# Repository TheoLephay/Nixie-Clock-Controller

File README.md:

# Nixie clock - Divergence Meter

I wanted to make a 8-tube design to match Steins Gate's divergence meter and to have more display capabilities.

This is build with original IN-14 (180VDC) Nixie tubes manufactured in the 70s in the Soviet Union.

## How to use

- On power on, if a wifi access point has been provided before, it will try to connect to it.
- Otherwise (if no AP, or if connection fails) it will display blinking dots and it will turn into an access point named "ESP32_Nixie".
  Connect to it, open the clock's IP on a web page, and provide wifi SSID and password. The clock will then
  try to connect to the provided wifi AP.
- It will start displaying the time. You can press the toggle swith (long or short press) to change modes.

## How to build

There should be most of the design files for software and hardware to reproduce it.

Except:
- Tubes that I bought on Ebay
- The BOM is not exaclty complete but all the electronics to build the PCB are there. What's missing is
    - the Molex ribbon cables (check the reference of the connectors and find the matching ones)
    - few pin headers and jumpers
- The case that is home made with some very specific tools.

---

## Hardware

See hardware/*.pdf for the design sheet and layer views. All Kicad design files should be present to build them and the gerber files.

key facts:

- Made for 8 IN-14 tubes
- HV DCDC generator made on board, based on [this design](https://nick.desmith.net/Electronics/NixiePSU.html)
- HV open drain shift registers HV5622 (no multiplexing)
- ESP32C3 module
- Most of the components are solderable with a soldering iron (except the ESP32 because of the pads underneath, heat gun or hot plate required + stencil)

#### Version 1.1 updates:

Fixed HV5622 footprint, used a bigger DCDC FET (Vds rated >250V), Reduced GPIO9 cap size to avoid starting in DL mode, and added PD resistors to the level shifters' NFETs.

### Issues

The feedback line of the DCDC is picking up noise which creates a visible dimming oscillation at around 20Hz (50Vpp). At high load it even makes the DCDC saturate.
I fixed it by adding a small cap (100pF) on FB pin. 0603 size is perfect to sit between SHDN and FB pins of the MAX1771.

My DCDC has only a ~70% efficiency which is not super good compared to the original design (85%), I probably did a poor layout job. But in practice it does not matter since currents involved are small.

## Software

key facts:

- Using ESP-IDF VSCode extension v5.2.1
- Programming via UART (two buttons on the board to get the ESP in download mode)
- Has a "maintenance" routine timer to cycle the cathodes lit to prevent cathode poisonning.

More modes to be coming (with a connected weather station it will be able to display temp/HR...).

- main/src/Connectivity.c - wifi state machine, mDNS & SNTP setup.
- main/src/HV5622.c - Bit banging shift register driver.
- main/src/ModeSwitch.c - Driver for the toggle switch.
- main/src/NixieDisplay.c - simple driver to display data on the 8 tubes using the shift registers.
- main/src/NixieHttpServer.c - Web control page
- main/src/SmartClock.c - core logic of the clock to display time, handle different modes.
- main/src/Storage.c - NVS wrapper for storing wifi credentials.

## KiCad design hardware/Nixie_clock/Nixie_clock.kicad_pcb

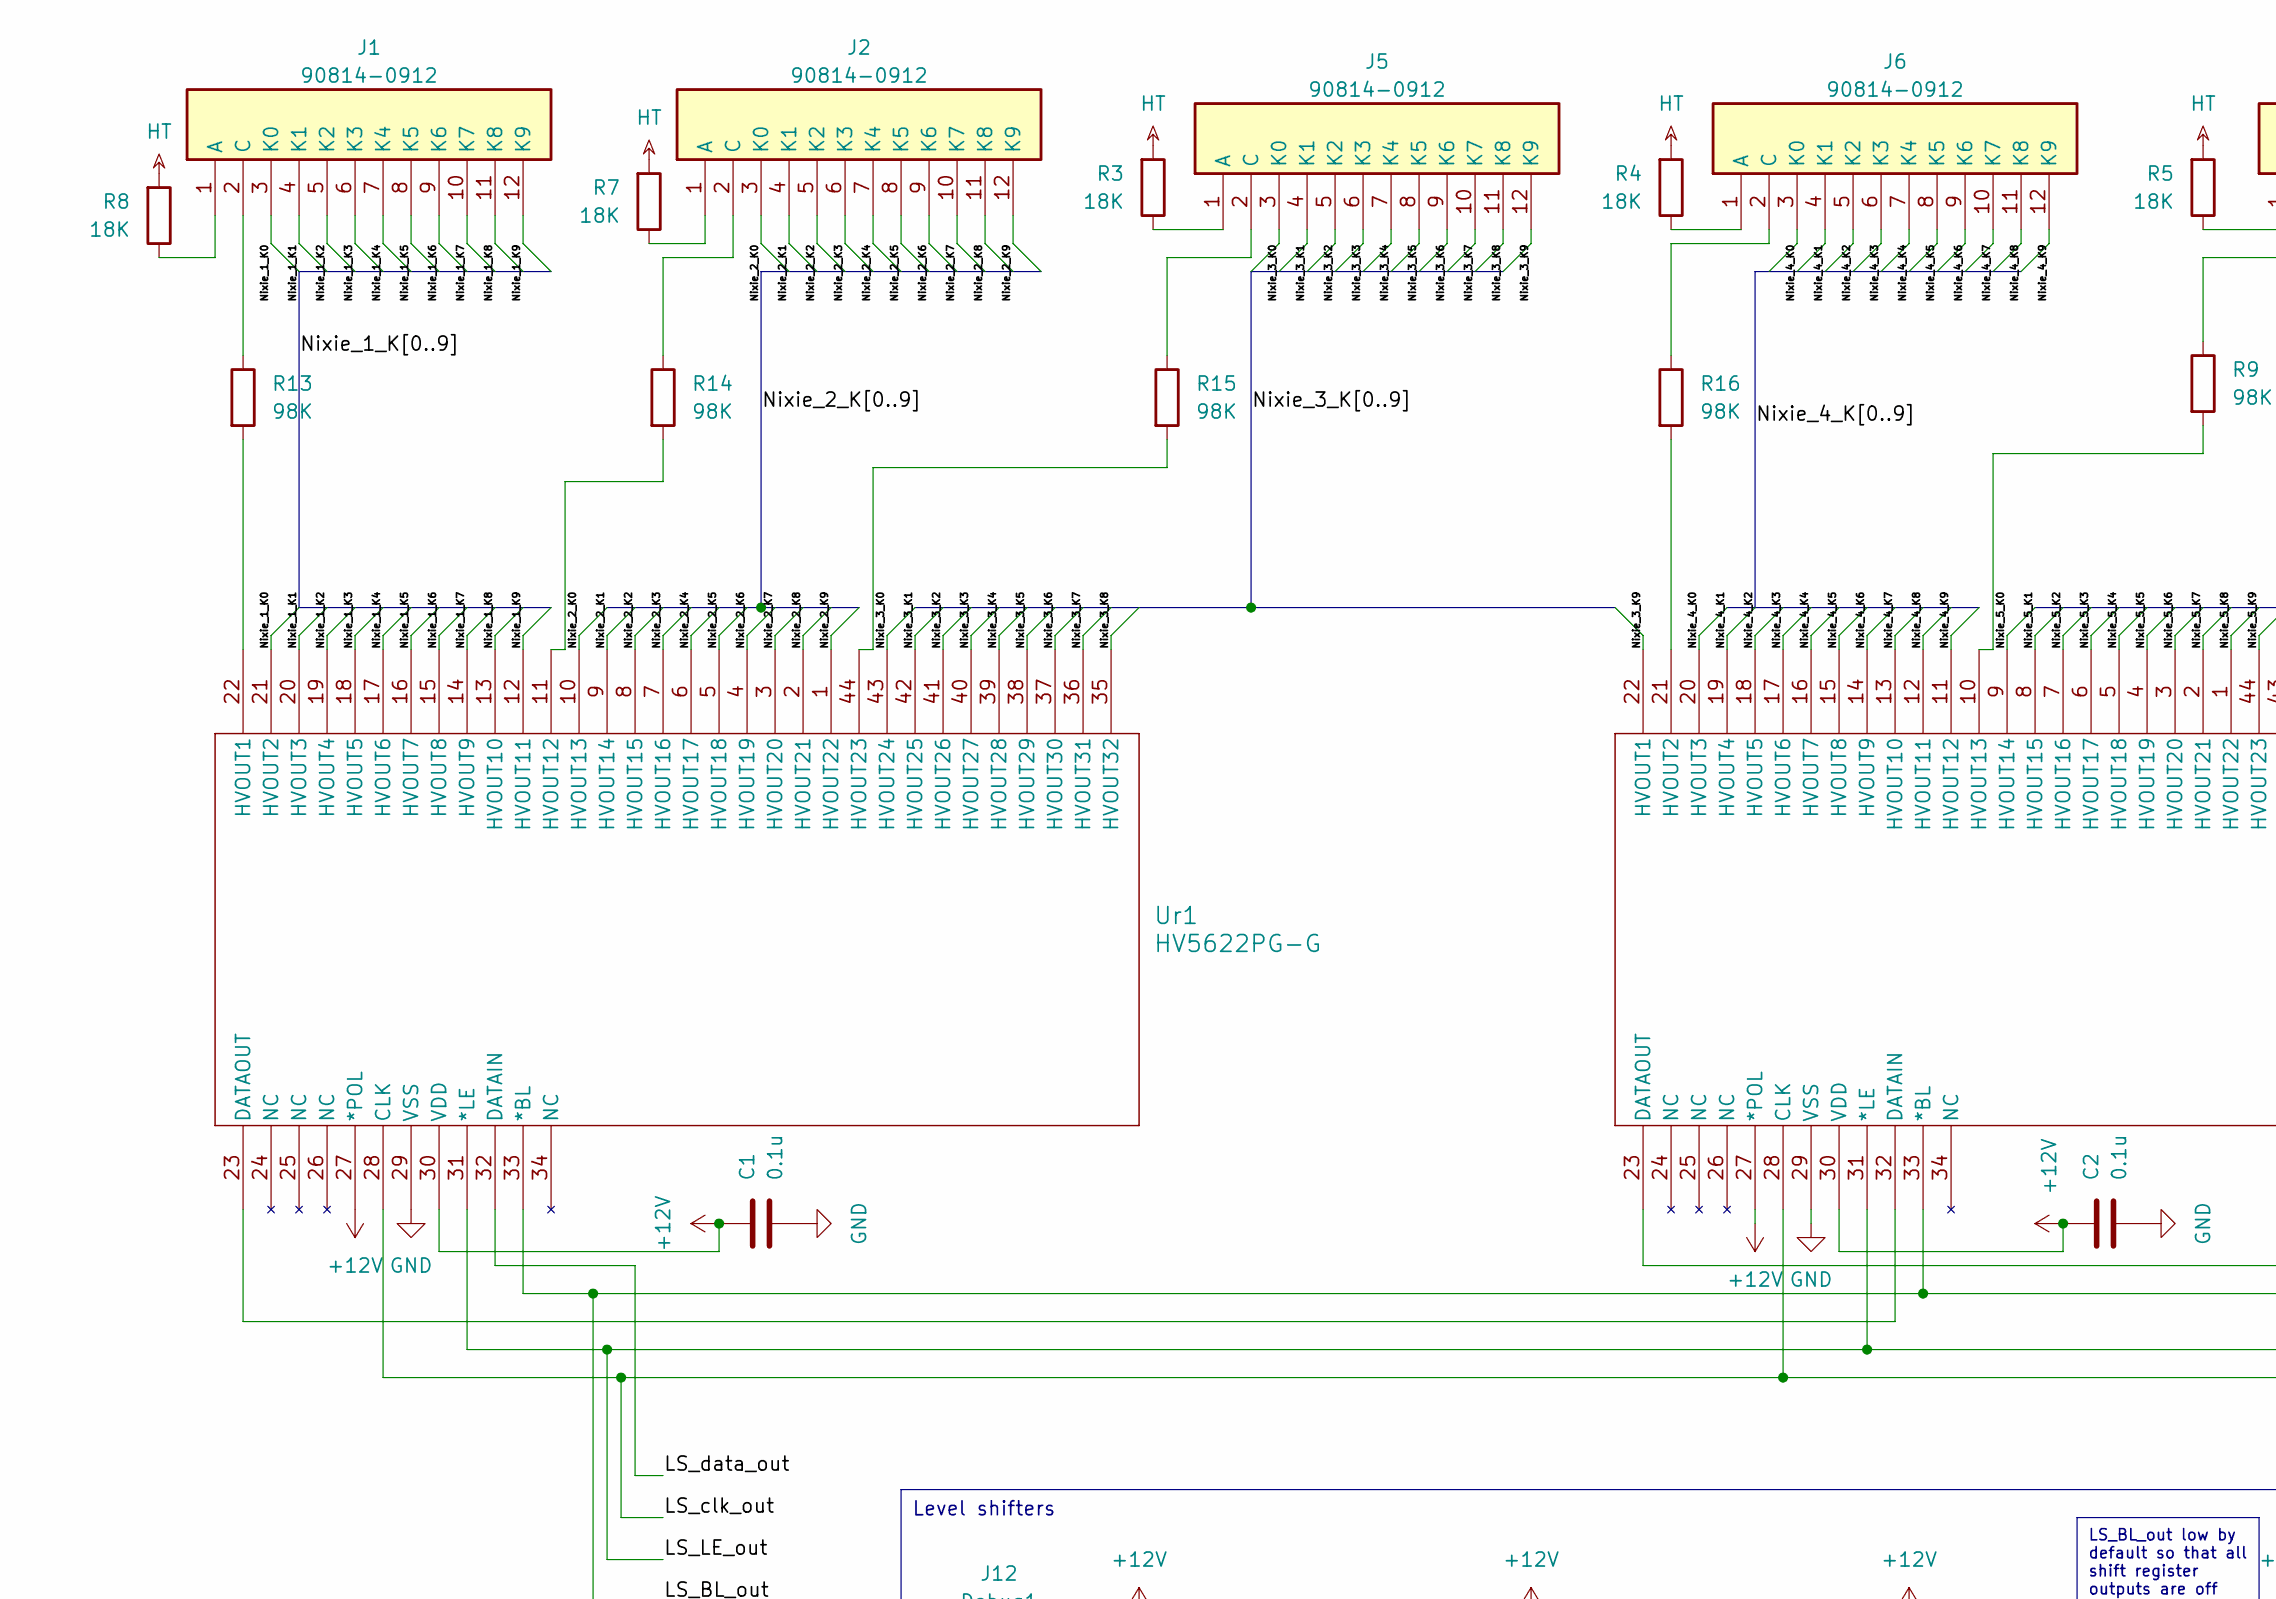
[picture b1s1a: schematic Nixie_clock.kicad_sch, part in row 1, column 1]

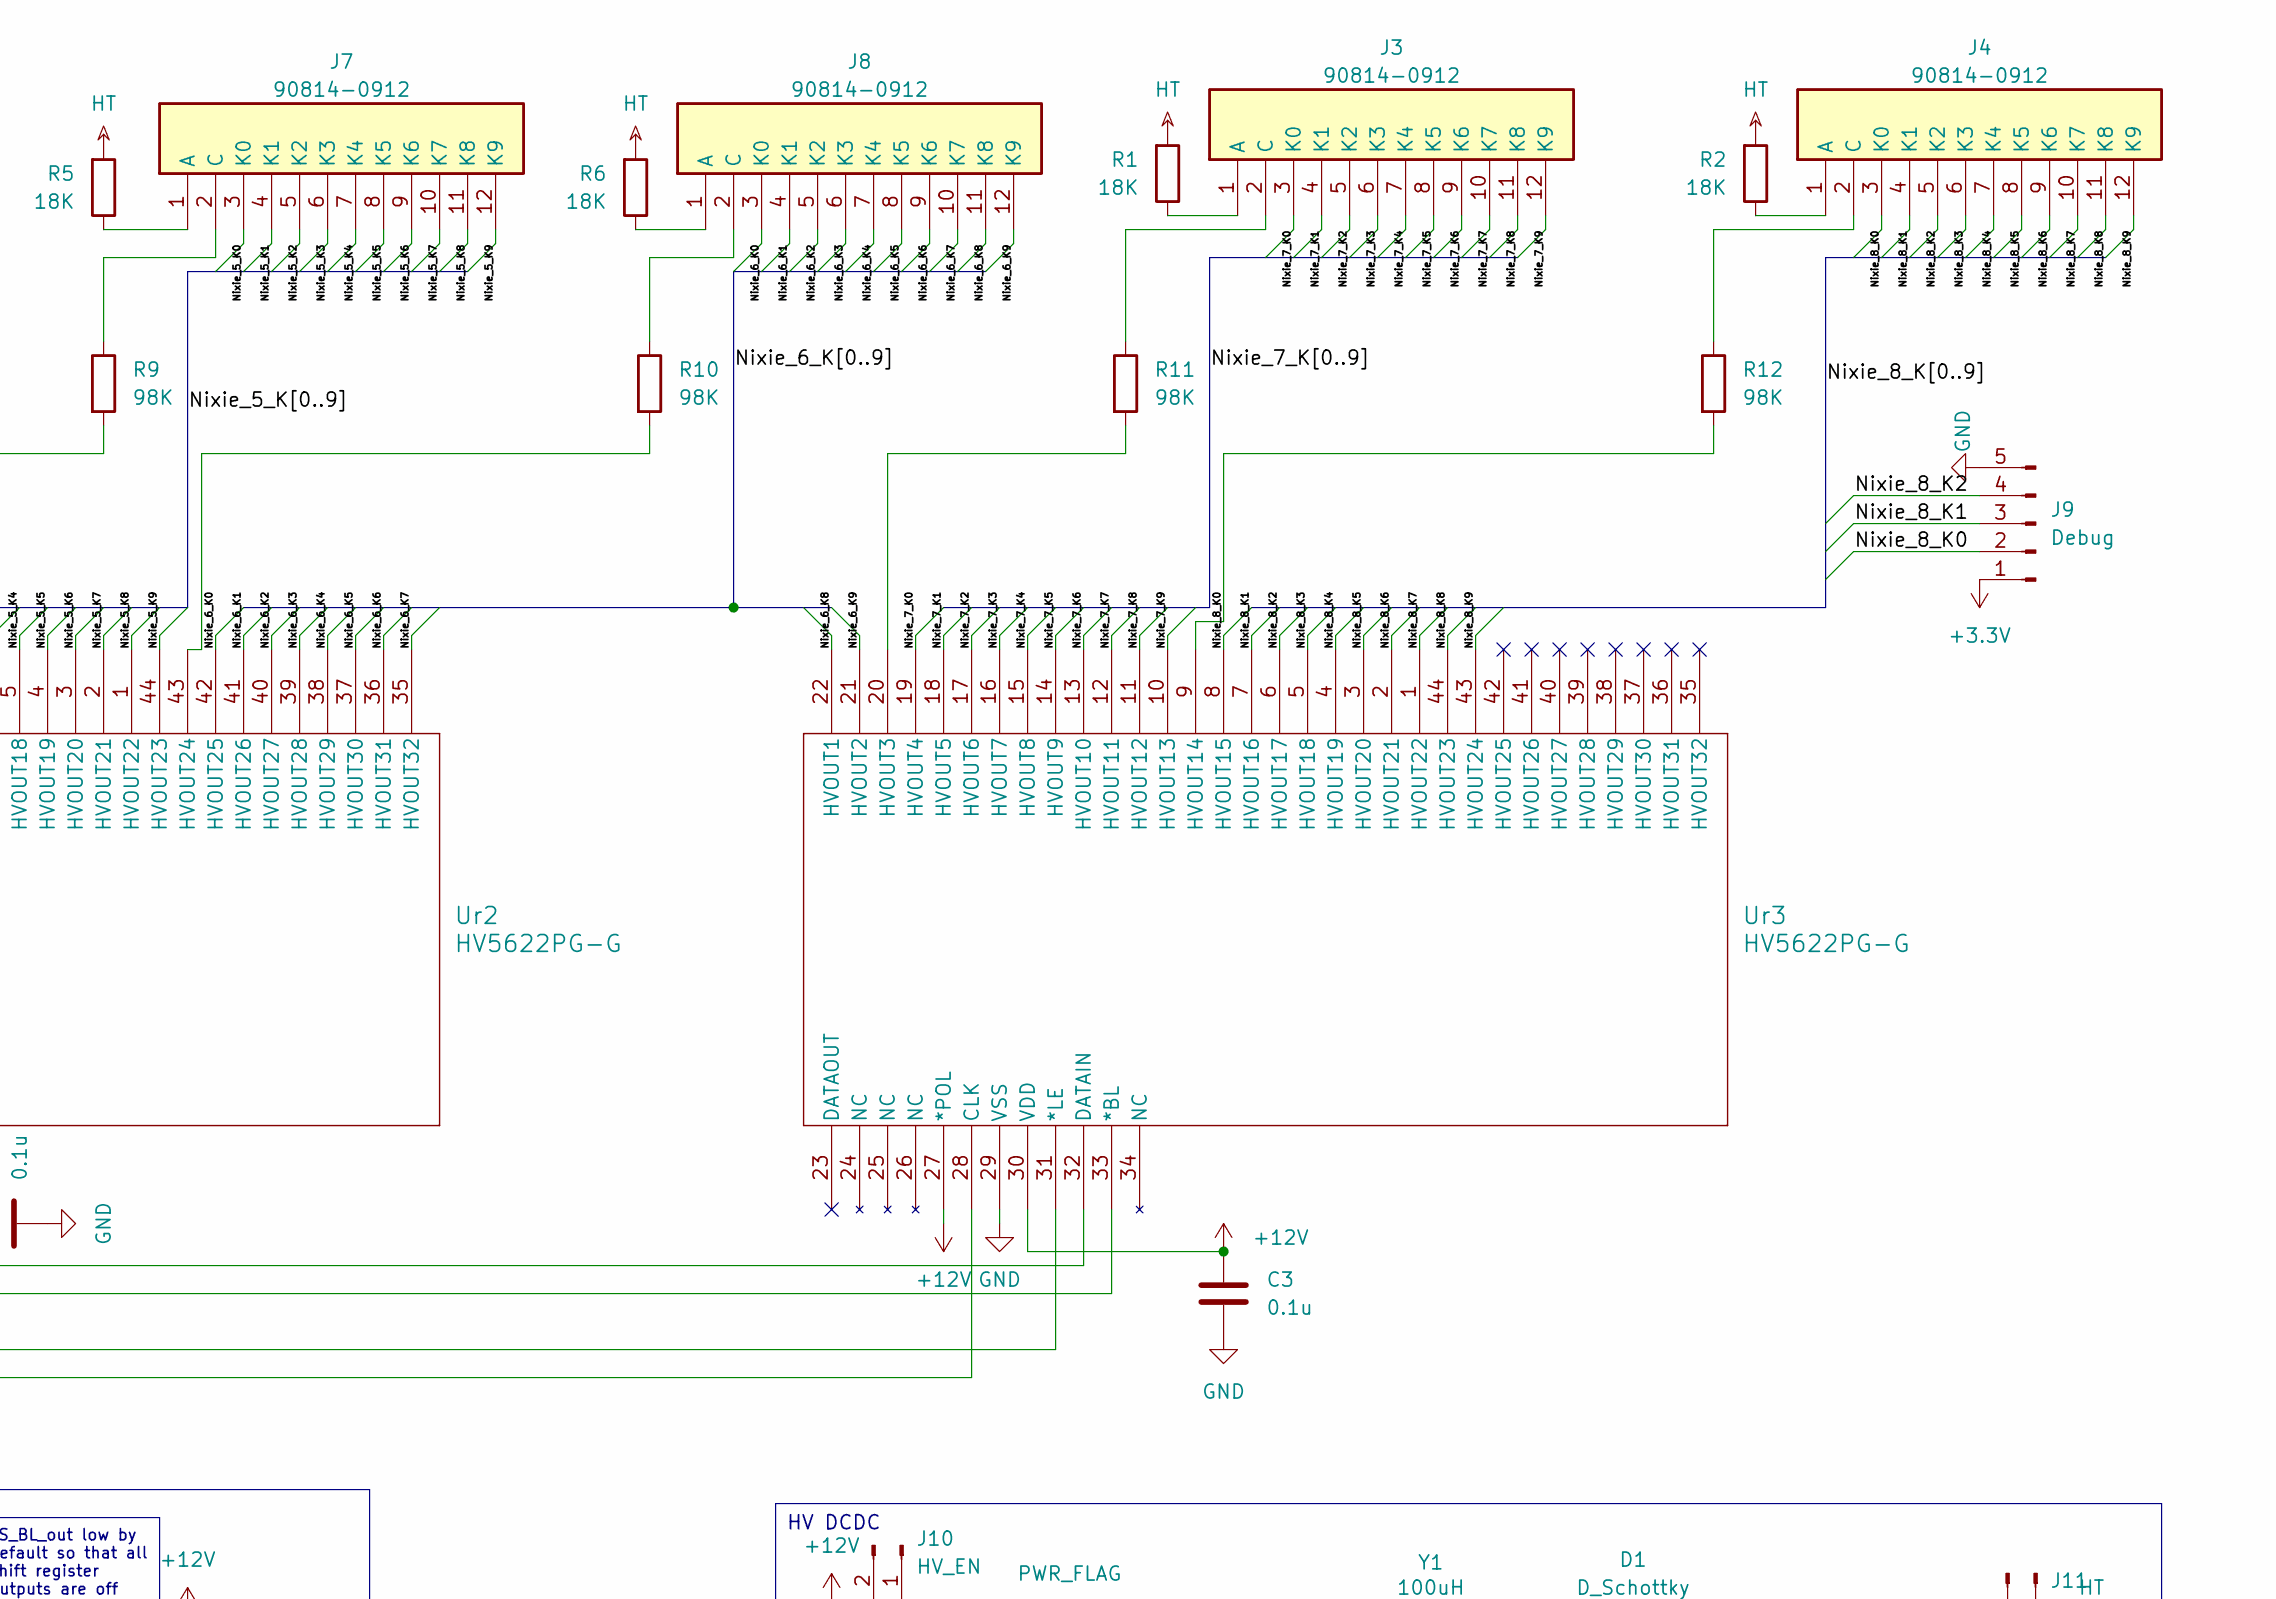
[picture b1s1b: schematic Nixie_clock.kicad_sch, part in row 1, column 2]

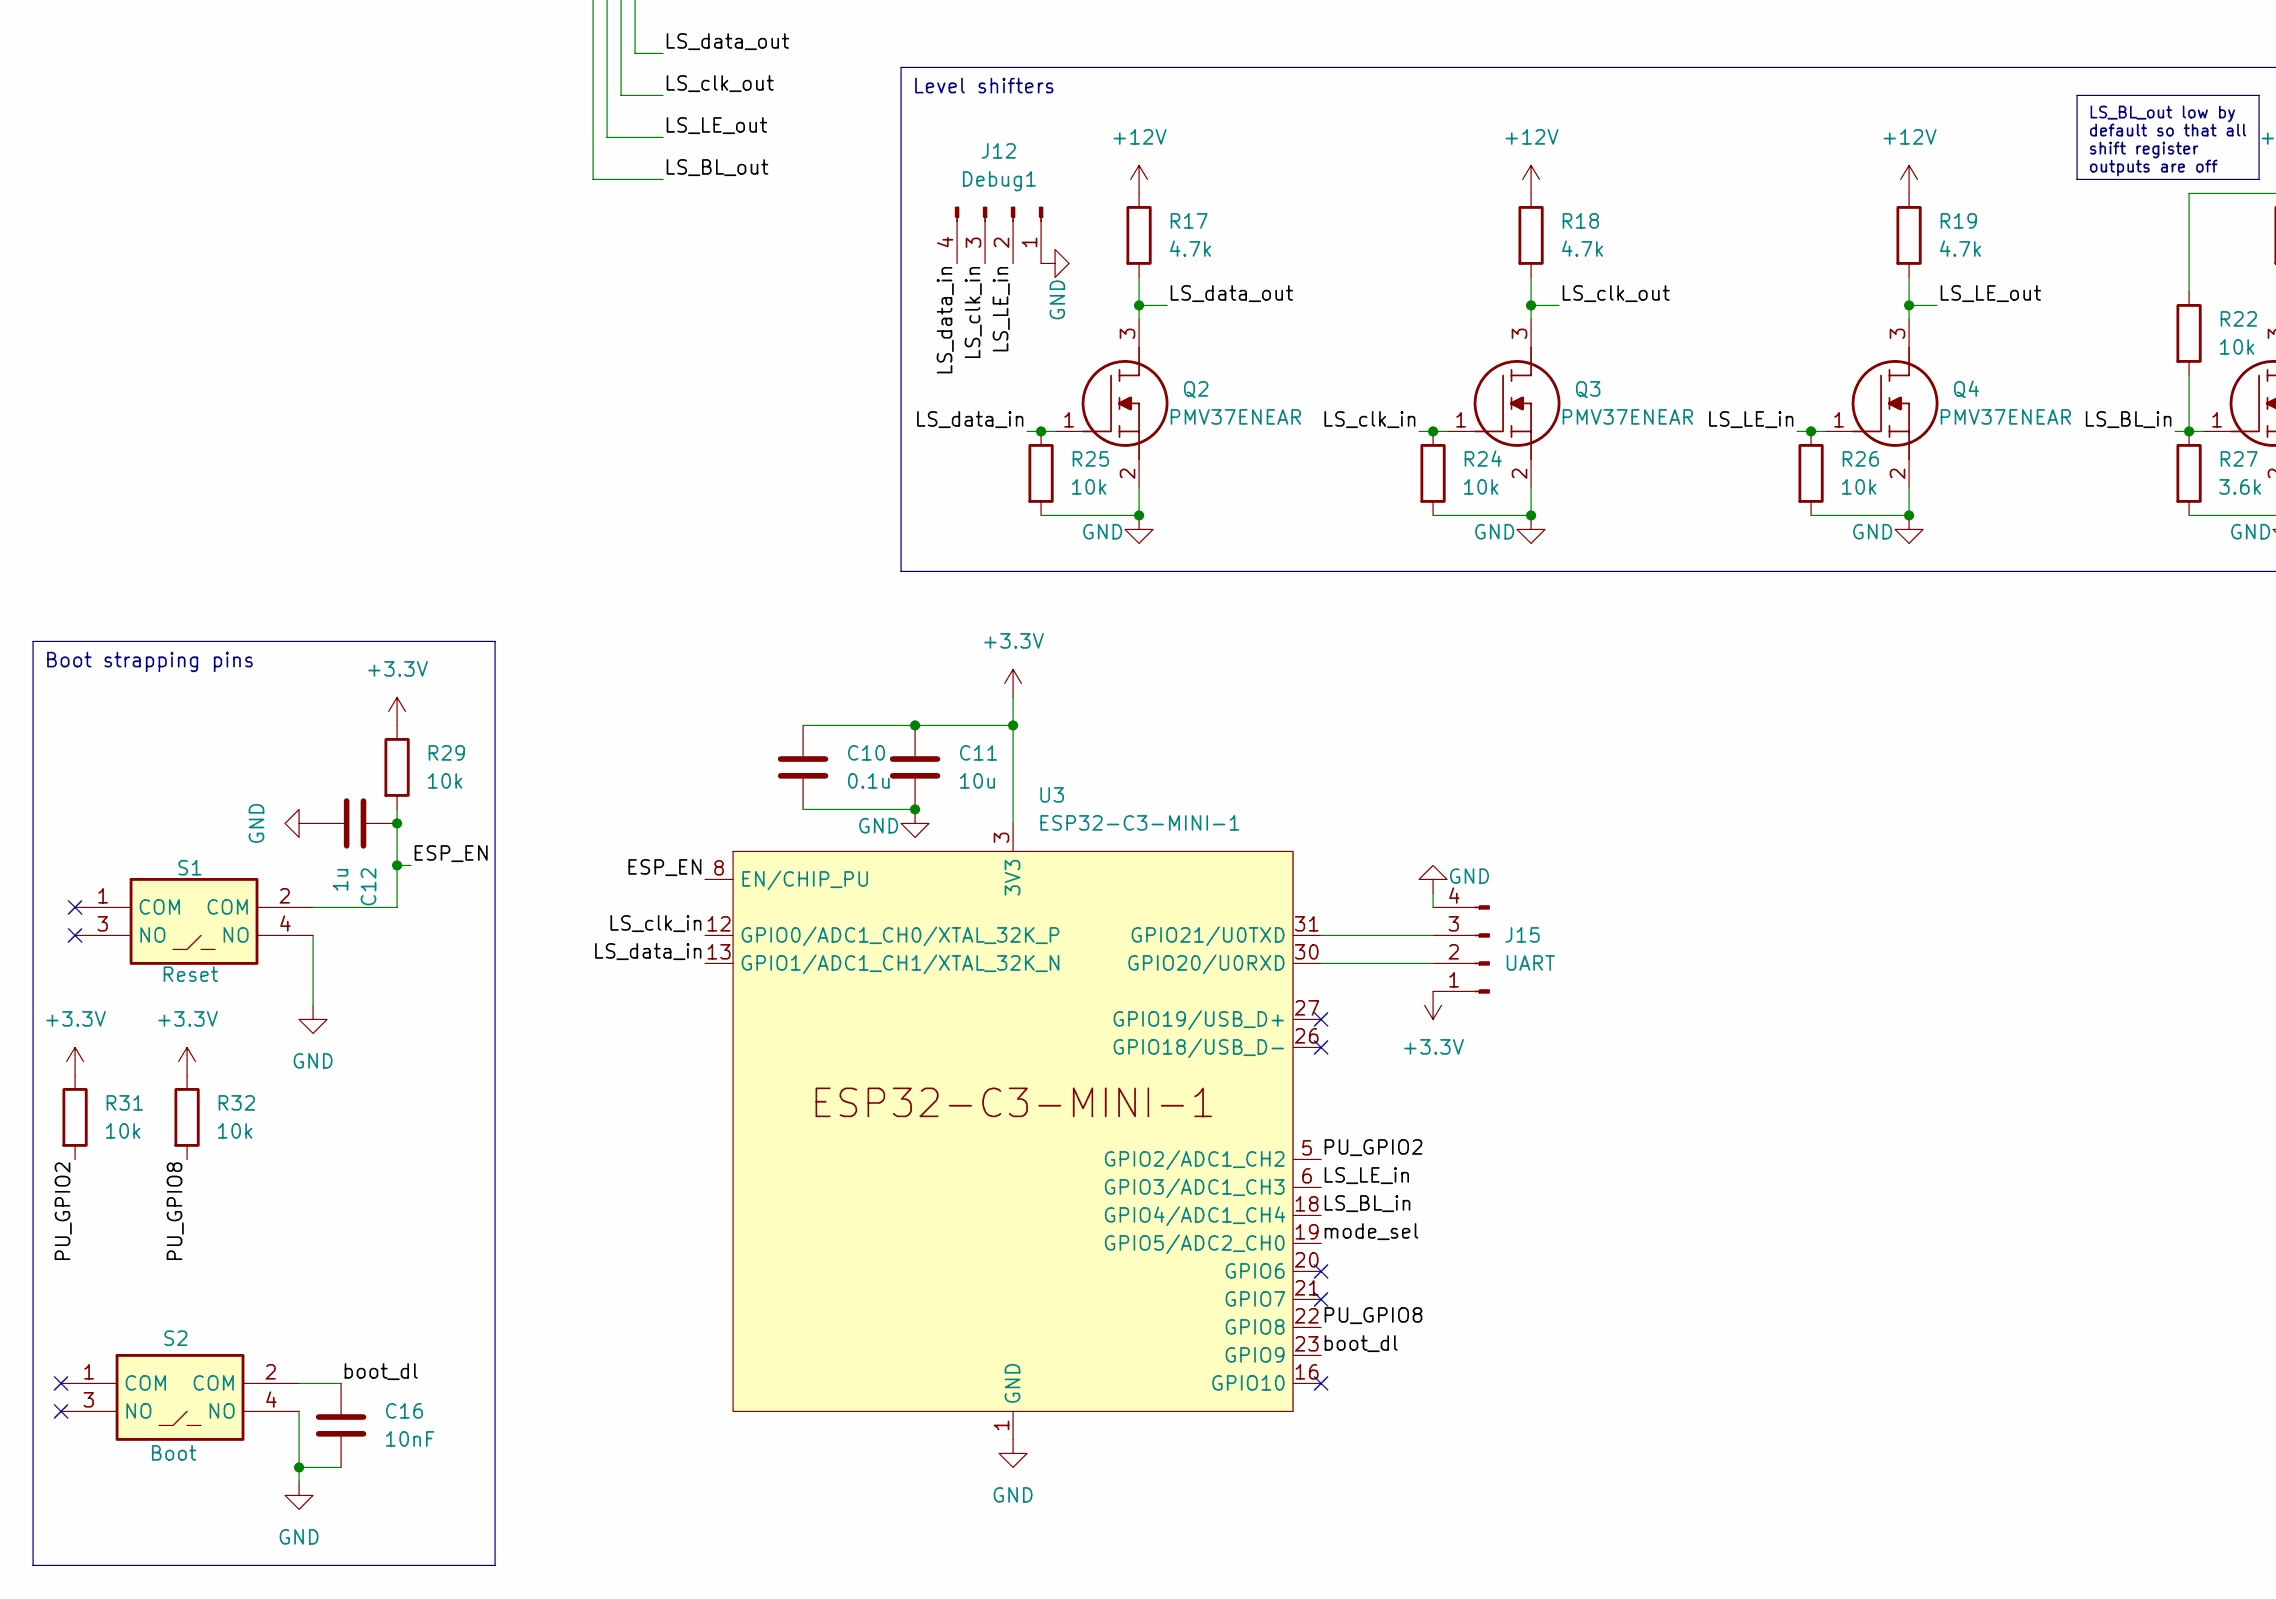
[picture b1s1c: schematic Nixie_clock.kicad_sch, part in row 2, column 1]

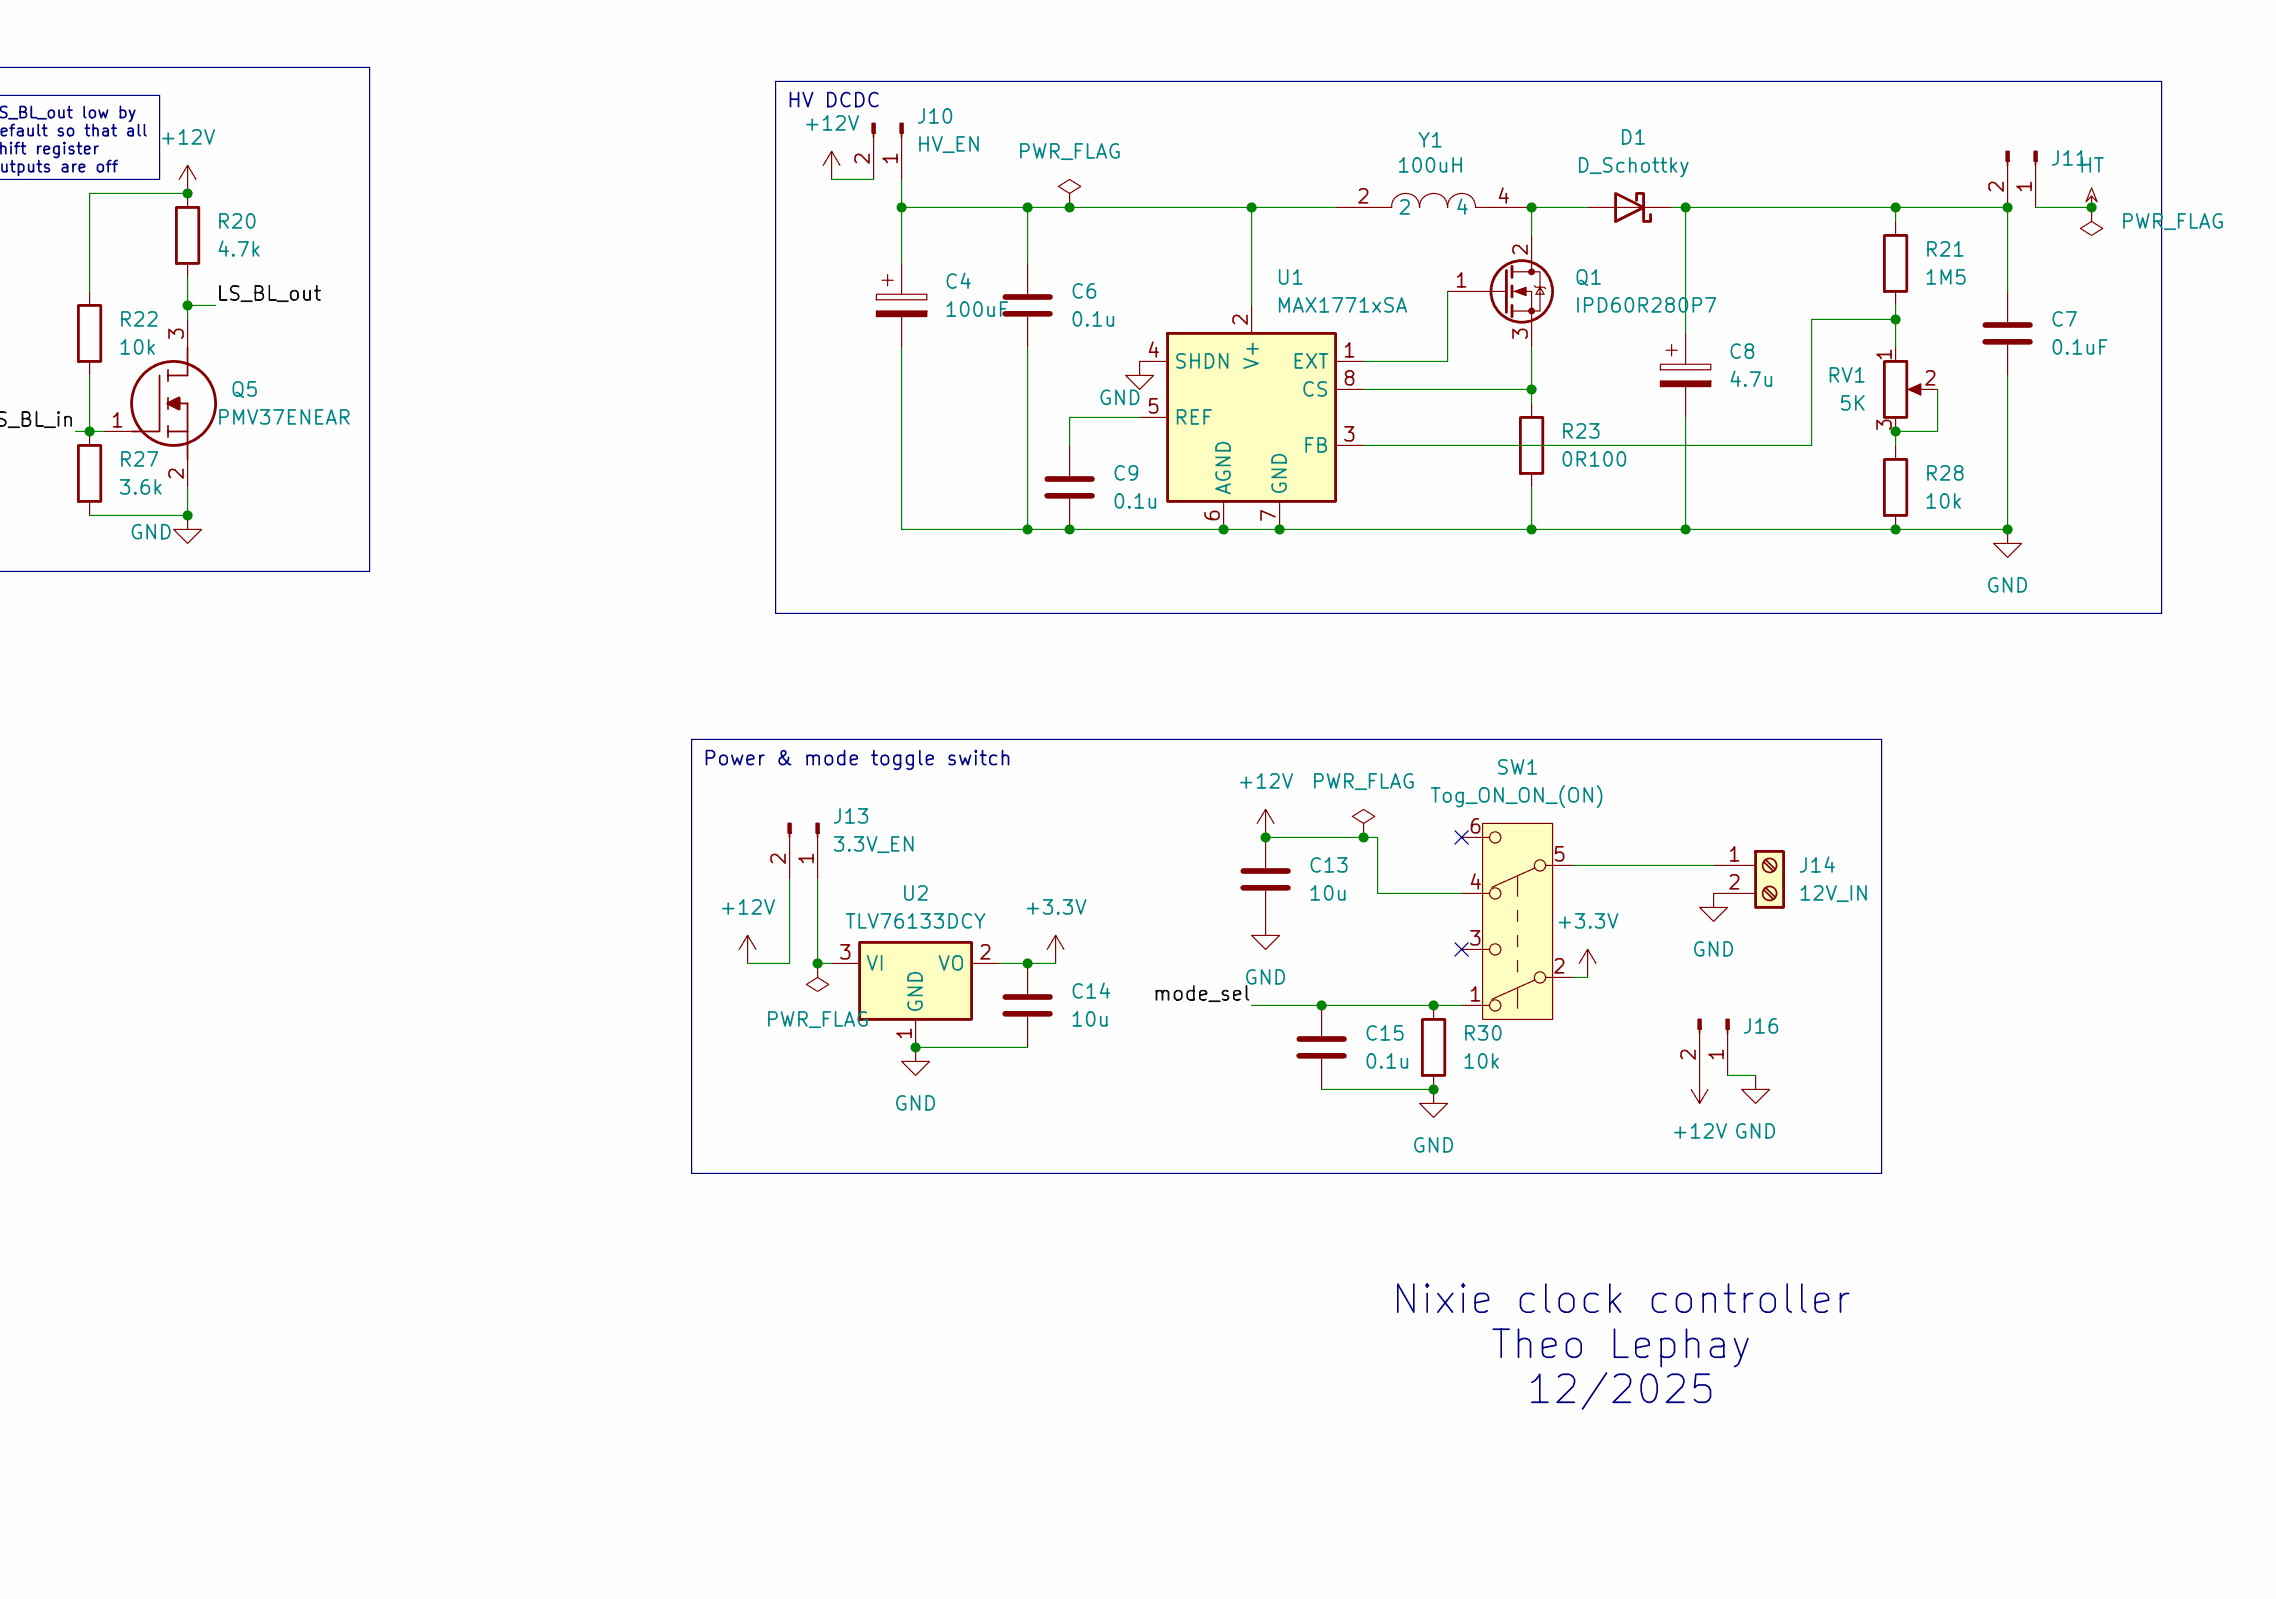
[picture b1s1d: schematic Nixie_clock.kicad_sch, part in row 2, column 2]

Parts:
C1, C2, C3, C6, C9, C10, C15: 0.1u; C_1206_3216Metric_Pad1.33x1.80mm_HandSolder
C4: 100uF; CP_EIA-7343-31_Kemet-D_HandSolder
C7: 0.1uF; C_1206_3216Metric_Pad1.33x1.80mm_HandSolder
C8: 4.7u; CP_Radial_D8.0mm_P3.50mm
C11, C13, C14: 10u; C_1206_3216Metric_Pad1.33x1.80mm_HandSolder
C12: 1u; C_1206_3216Metric_Pad1.33x1.80mm_HandSolder
C16: 10nF; C_1206_3216Metric_Pad1.33x1.80mm_HandSolder
D1: D_Schottky; D_2010_5025Metric_Pad1.52x2.65mm_HandSolder
J1, J2, J3, J4, J5, J6, J7, J8: 90814-0912; Molex_Picoflex_90814-0012_2x06_P1.27mm_Vertical; Mouser Part Number 538-90814-0912
J9: Debug; PinHeader_1x05_P2.54mm_Vertical
J10: HV_EN; PinHeader_1x02_P2.54mm_Vertical
J11, J16: Conn_01x02_Pin; PinHeader_1x02_P2.54mm_Vertical
J12: Debug1; PinHeader_1x04_P2.54mm_Vertical
J13: 3.3V_EN; PinHeader_1x02_P2.54mm_Vertical
J14: 12V_IN; TerminalBlock_MaiXu_MX126-5.0-02P_1x02_P5.00mm
J15: UART; PinSocket_1x04_P2.54mm_Horizontal
Q1: IPD60R280P7; TO-252-2
Q2, Q3, Q4, Q5: PMV37ENEAR; SOT95P230X110-3N; Mouser Part Number 771-PMV37ENEAR
R1, R2, R3, R4, R5, R6, R7, R8: 18K; R_1206_3216Metric_Pad1.30x1.75mm_HandSolder
R9, R10, R11, R12, R13, R14, R15, R16: 98K; R_1206_3216Metric_Pad1.30x1.75mm_HandSolder
R17, R18, R19, R20: 4.7k; R_1206_3216Metric_Pad1.30x1.75mm_HandSolder
R21: 1M5; R_2010_5025Metric_Pad1.40x2.65mm_HandSolder
R22, R24, R25, R26, R28, R29, R30, R31, R32: 10k; R_1206_3216Metric_Pad1.30x1.75mm_HandSolder
R23: 0R100; R_1210_3225Metric_Pad1.30x2.65mm_HandSolder
R27: 3.6k; R_1206_3216Metric_Pad1.30x1.75mm_HandSolder
RV1: 5K; Potentiometer_Bourns_3296W_Vertical
S1: Reset; TL6150BF160QG; Mouser Part Number 612-TL6150BF160QG
S2: Boot; TL6150BF160QG; Mouser Part Number 612-TL6150BF160QG
SW1: Tog_ON_ON_(ON); Molex_Picoflex_90814-0006_2x03_P1.27mm_Vertical
U1: MAX1771xSA; SO-8_3.9x4.9mm_P1.27mm
U2: TLV76133DCY; SOT-223-3_TabPin2
U3: ESP32-C3-MINI-1
Ur1, Ur2, Ur3: HV5622PG-G; QFP44_10x10MC_MCH-L
Y1: 100uH; AIUR-08; Mouser Part Number 815-AIUR-08-101K

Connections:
+3.3V: C10.1, C11.1, C14.1, J9.1, J15.1, R29.1, R31.1, R32.1, SW1.2 (B), U2.2 (VO), U3.3 (3V3)
+12V: C1.1, C2.1, C3.1, C13.1, J10.2, J13.2, J16.2, R17.1, R18.1, R19.1, R20.1, R22.1, SW1.4 (A), Ur1.27 (*POL), Ur1.30 (VDD), Ur2.27 (*POL), Ur2.30 (VDD), Ur3.27 (*POL), Ur3.30 (VDD)
/ESP_EN: C12.1, R29.2, S1.2 (COM), U3.8 (EN/CHIP_PU)
/LS_BL_in: Q5.1, R22.2, R27.1, U3.18 (GPIO4/ADC1_CH4)
/LS_BL_out: Q5.3, R20.2, Ur1.33 (*BL), Ur2.33 (*BL), Ur3.33 (*BL)
/LS_LE_in: J12.2, Q4.1, R26.1, U3.6 (GPIO3/ADC1_CH3)
/LS_LE_out: Q4.3, R19.2, Ur1.31 (*LE), Ur2.31 (*LE), Ur3.31 (*LE)
/LS_clk_in: J12.3, Q3.1, R24.1, U3.12 (GPIO0/ADC1_CH0/XTAL_32K_P)
/LS_clk_out: Q3.3, R18.2, Ur1.28 (CLK), Ur2.28 (CLK), Ur3.28 (CLK)
/LS_data_in: J12.4, Q2.1, R25.1, U3.13 (GPIO1/ADC1_CH1/XTAL_32K_N)
/LS_data_out: Q2.3, R17.2, Ur1.32 (DATAIN)
/Nixie_1_K0: J1.3 (K0), Ur1.21 (HVOUT2)
/Nixie_1_K1: J1.4 (K1), Ur1.20 (HVOUT3)
/Nixie_1_K2: J1.5 (K2), Ur1.19 (HVOUT4)
/Nixie_1_K3: J1.6 (K3), Ur1.18 (HVOUT5)
/Nixie_1_K4: J1.7 (K4), Ur1.17 (HVOUT6)
/Nixie_1_K5: J1.8 (K5), Ur1.16 (HVOUT7)
/Nixie_1_K6: J1.9 (K6), Ur1.15 (HVOUT8)
/Nixie_1_K7: J1.10 (K7), Ur1.14 (HVOUT9)
/Nixie_1_K8: J1.11 (K8), Ur1.13 (HVOUT10)
/Nixie_1_K9: J1.12 (K9), Ur1.12 (HVOUT11)
/Nixie_2_K0: J2.3 (K0), Ur1.10 (HVOUT13)
/Nixie_2_K1: J2.4 (K1), Ur1.9 (HVOUT14)
/Nixie_2_K2: J2.5 (K2), Ur1.8 (HVOUT15)
/Nixie_2_K3: J2.6 (K3), Ur1.7 (HVOUT16)
/Nixie_2_K4: J2.7 (K4), Ur1.6 (HVOUT17)
/Nixie_2_K5: J2.8 (K5), Ur1.5 (HVOUT18)
/Nixie_2_K6: J2.9 (K6), Ur1.4 (HVOUT19)
/Nixie_2_K7: J2.10 (K7), Ur1.3 (HVOUT20)
/Nixie_2_K8: J2.11 (K8), Ur1.2 (HVOUT21)
/Nixie_2_K9: J2.12 (K9), Ur1.1 (HVOUT22)
/Nixie_3_K0: J5.3 (K0), Ur1.43 (HVOUT24)
/Nixie_3_K1: J5.4 (K1), Ur1.42 (HVOUT25)
/Nixie_3_K2: J5.5 (K2), Ur1.41 (HVOUT26)
/Nixie_3_K3: J5.6 (K3), Ur1.40 (HVOUT27)
/Nixie_3_K4: J5.7 (K4), Ur1.39 (HVOUT28)
/Nixie_3_K5: J5.8 (K5), Ur1.38 (HVOUT29)
/Nixie_3_K6: J5.9 (K6), Ur1.37 (HVOUT30)
/Nixie_3_K7: J5.10 (K7), Ur1.36 (HVOUT31)
/Nixie_3_K8: J5.11 (K8), Ur1.35 (HVOUT32)
/Nixie_3_K9: J5.12 (K9), Ur2.22 (HVOUT1)
/Nixie_4_K0: J6.3 (K0), Ur2.20 (HVOUT3)
/Nixie_4_K1: J6.4 (K1), Ur2.19 (HVOUT4)
/Nixie_4_K2: J6.5 (K2), Ur2.18 (HVOUT5)
/Nixie_4_K3: J6.6 (K3), Ur2.17 (HVOUT6)
/Nixie_4_K4: J6.7 (K4), Ur2.16 (HVOUT7)
/Nixie_4_K5: J6.8 (K5), Ur2.15 (HVOUT8)
/Nixie_4_K6: J6.9 (K6), Ur2.14 (HVOUT9)
/Nixie_4_K7: J6.10 (K7), Ur2.13 (HVOUT10)
/Nixie_4_K8: J6.11 (K8), Ur2.12 (HVOUT11)
/Nixie_4_K9: J6.12 (K9), Ur2.11 (HVOUT12)
/Nixie_5_K0: J7.3 (K0), Ur2.9 (HVOUT14)
/Nixie_5_K1: J7.4 (K1), Ur2.8 (HVOUT15)
/Nixie_5_K2: J7.5 (K2), Ur2.7 (HVOUT16)
/Nixie_5_K3: J7.6 (K3), Ur2.6 (HVOUT17)
/Nixie_5_K4: J7.7 (K4), Ur2.5 (HVOUT18)
/Nixie_5_K5: J7.8 (K5), Ur2.4 (HVOUT19)
/Nixie_5_K6: J7.9 (K6), Ur2.3 (HVOUT20)
/Nixie_5_K7: J7.10 (K7), Ur2.2 (HVOUT21)
/Nixie_5_K8: J7.11 (K8), Ur2.1 (HVOUT22)
/Nixie_5_K9: J7.12 (K9), Ur2.44 (HVOUT23)
/Nixie_6_K0: J8.3 (K0), Ur2.42 (HVOUT25)
/Nixie_6_K1: J8.4 (K1), Ur2.41 (HVOUT26)
/Nixie_6_K2: J8.5 (K2), Ur2.40 (HVOUT27)
/Nixie_6_K3: J8.6 (K3), Ur2.39 (HVOUT28)
/Nixie_6_K4: J8.7 (K4), Ur2.38 (HVOUT29)
/Nixie_6_K5: J8.8 (K5), Ur2.37 (HVOUT30)
/Nixie_6_K6: J8.9 (K6), Ur2.36 (HVOUT31)
/Nixie_6_K7: J8.10 (K7), Ur2.35 (HVOUT32)
/Nixie_6_K8: J8.11 (K8), Ur3.22 (HVOUT1)
/Nixie_6_K9: J8.12 (K9), Ur3.21 (HVOUT2)
/Nixie_7_K0: J3.3 (K0), Ur3.19 (HVOUT4)
/Nixie_7_K1: J3.4 (K1), Ur3.18 (HVOUT5)
/Nixie_7_K2: J3.5 (K2), Ur3.17 (HVOUT6)
/Nixie_7_K3: J3.6 (K3), Ur3.16 (HVOUT7)
/Nixie_7_K4: J3.7 (K4), Ur3.15 (HVOUT8)
/Nixie_7_K5: J3.8 (K5), Ur3.14 (HVOUT9)
/Nixie_7_K6: J3.9 (K6), Ur3.13 (HVOUT10)
/Nixie_7_K7: J3.10 (K7), Ur3.12 (HVOUT11)
/Nixie_7_K8: J3.11 (K8), Ur3.11 (HVOUT12)
/Nixie_7_K9: J3.12 (K9), Ur3.10 (HVOUT13)
/Nixie_8_K0: J4.3 (K0), J9.2, Ur3.8 (HVOUT15)
/Nixie_8_K1: J4.4 (K1), J9.3, Ur3.7 (HVOUT16)
/Nixie_8_K2: J4.5 (K2), J9.4, Ur3.6 (HVOUT17)
/Nixie_8_K3: J4.6 (K3), Ur3.5 (HVOUT18)
/Nixie_8_K4: J4.7 (K4), Ur3.4 (HVOUT19)
/Nixie_8_K5: J4.8 (K5), Ur3.3 (HVOUT20)
/Nixie_8_K6: J4.9 (K6), Ur3.2 (HVOUT21)
/Nixie_8_K7: J4.10 (K7), Ur3.1 (HVOUT22)
/Nixie_8_K8: J4.11 (K8), Ur3.44 (HVOUT23)
/Nixie_8_K9: J4.12 (K9), Ur3.43 (HVOUT24)
/PU_GPIO2: R31.2, U3.5 (GPIO2/ADC1_CH2)
/PU_GPIO8: R32.2, U3.22 (GPIO8)
/boot_dl: C16.1, S2.2 (COM), U3.23 (GPIO9)
/mode_sel: C15.1, R30.1, SW1.1 (A), U3.19 (GPIO5/ADC2_CH0)
GND: C1.2, C2.2, C3.2, C4.2, C6.2, C7.2, C8.2, C9.2, C10.2, C11.2, C12.2, C13.2, C14.2, C15.2, C16.2, J9.5, J12.1, J14.2, J15.4, J16.1, Q2.2, Q3.2, Q4.2, Q5.2, R23.2, R24.2, R25.2, R26.2, R27.2, R28.2, R30.2, S1.4 (NO), S2.4 (NO), U1.4 (SHDN), U1.6 (AGND), U1.7 (GND), U2.1 (GND), U3.1 (GND), U3.2 (GND), U3.11 (GND), U3.14 (GND), U3.36 (GND), U3.37 (GND), U3.38 (GND), U3.39 (GND), U3.40 (GND), U3.41 (GND), U3.42 (GND), U3.43 (GND), U3.44 (GND), U3.45 (GND), U3.46 (GND), U3.47 (GND), U3.48 (GND), U3.49 (GND), U3.50 (GND), U3.51 (GND), U3.52 (GND), U3.53 (GND), Ur1.29 (VSS), Ur2.29 (VSS), Ur3.29 (VSS)
HT: J11.1, R1.2, R2.2, R3.2, R4.2, R5.2, R6.2, R7.2, R8.2
unnamed: D1.2 (A), Q1.2 (D), Y1.4
unnamed: C7.1, C8.1, D1.1 (K), J11.2, R21.1
unnamed: J1.1 (A), R8.1
unnamed: J1.2 (C), R13.1
unnamed: J2.1 (A), R7.1
unnamed: J2.2 (C), R14.1
unnamed: J3.1 (A), R1.1
unnamed: J3.2 (C), R11.1
unnamed: J4.1 (A), R2.1
unnamed: J4.2 (C), R12.1
unnamed: J5.1 (A), R3.1
unnamed: J5.2 (C), R15.1
unnamed: J6.1 (A), R4.1
unnamed: J6.2 (C), R16.1
unnamed: J7.1 (A), R5.1
unnamed: J7.2 (C), R9.1
unnamed: J8.1 (A), R6.1
unnamed: J8.2 (C), R10.1
unnamed: C4.1, C6.1, J10.1, U1.2 (V+), Y1.2
unnamed: J13.1, U2.3 (VI)
unnamed: J14.1, SW1.5 (B)
unnamed: J15.2, U3.30 (GPIO20/U0RXD)
unnamed: J15.3, U3.31 (GPIO21/U0TXD)
unnamed: Q1.1 (G), U1.1 (EXT)
unnamed: Q1.3 (S), R23.1, U1.8 (CS)
unnamed: R28.1, RV1.2, RV1.3
unnamed: R21.2, RV1.1, U1.3 (FB)
unnamed: C9.1, U1.5 (REF)
unnamed: Ur1.23 (DATAOUT), Ur2.32 (DATAIN)
unnamed: R13.2, Ur1.22 (HVOUT1)
unnamed: R14.2, Ur1.11 (HVOUT12)
unnamed: R15.2, Ur1.44 (HVOUT23)
unnamed: Ur2.23 (DATAOUT), Ur3.32 (DATAIN)
unnamed: R16.2, Ur2.21 (HVOUT2)
unnamed: R9.2, Ur2.10 (HVOUT13)
unnamed: R10.2, Ur2.43 (HVOUT24)
unnamed: R11.2, Ur3.20 (HVOUT3)
unnamed: R12.2, Ur3.9 (HVOUT14)

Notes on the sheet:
Nixie clock controller Theo Lephay 12/2025
HV DCDC
Power & mode toggle switch
LS_BL_out low by default so that all shift register outputs are off
Boot strapping pins
Level shifters

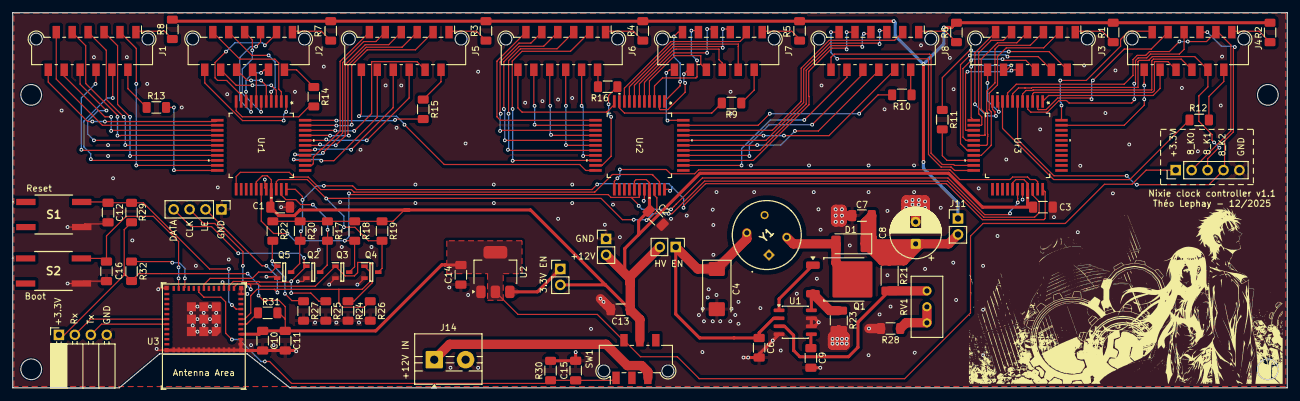
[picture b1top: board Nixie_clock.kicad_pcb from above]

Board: 2 copper layers, 203.2 x 59.8 mm, 80 parts (0 on the bottom side), 135 nets.

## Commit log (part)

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2025-12-09 init
2025-12-09 readme
2026-01-28 Hardware revision 1.1
    Fix: HV5622 pad spacing, use bigger DCDC FET, add LS NFETs PD resistors, Minor layout fixes.
2026-01-28 remove unused libs, update readme & pdf
2026-03-31 all software up to wifi STA/AP state machine & web server placeholder
2026-03-31 license MIT
2026-04-01 WIP: credential Storage, wifi cred form, quick and dirty fix for the state to avoid AP>STA race condition.
2026-05-31 Connectivity has its own task & event queue
2026-06-06 better web page with mode change.
2026-06-06 clock finally here !
